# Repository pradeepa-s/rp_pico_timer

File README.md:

# rp_pico_timer
A simple timer that is started as a reminder to drink water.

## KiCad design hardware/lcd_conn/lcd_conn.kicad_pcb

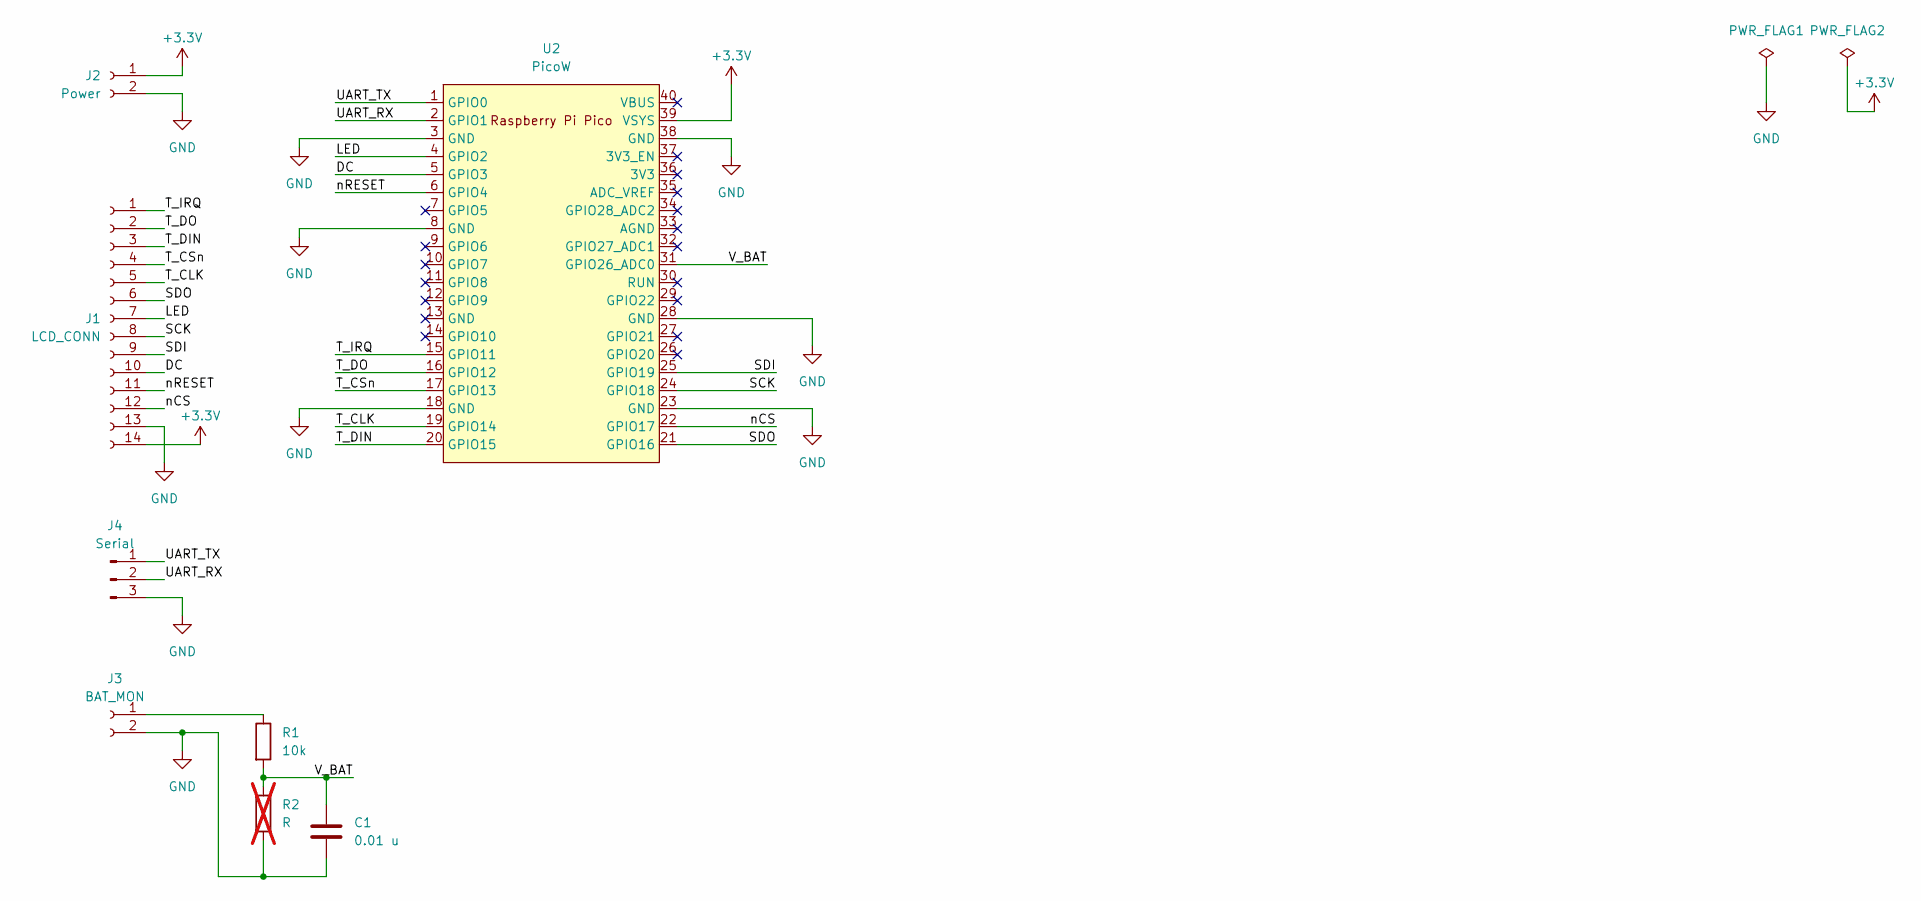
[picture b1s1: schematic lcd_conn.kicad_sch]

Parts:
C1: 0.01 u; C_Disc_D3.0mm_W2.0mm_P2.50mm
J1: LCD_CONN; PinSocket_1x14_P2.54mm_Vertical
J2: Power; PinHeader_1x02_P2.54mm_Vertical
J3: BAT_MON; PinHeader_1x02_P2.54mm_Vertical
J4: Serial; PinHeader_1x03_P2.54mm_Vertical
R1: 10k; R_Axial_DIN0207_L6.3mm_D2.5mm_P10.16mm_Horizontal
R2: R; R_Axial_DIN0207_L6.3mm_D2.5mm_P10.16mm_Horizontal; not fitted
U2: PicoW; RPi_PicoW_SMD_TH_CONN

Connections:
+3.3V: J1.14, J2.1, U2.39 (VSYS)
/DC: J1.10, U2.5 (GPIO3)
/LED: J1.7, U2.4 (GPIO2)
/SCK: J1.8, U2.24 (GPIO18)
/SDI: J1.9, U2.25 (GPIO19)
/SDO: J1.6, U2.21 (GPIO16)
/T_CLK: J1.5, U2.19 (GPIO14)
/T_CSn: J1.4, U2.17 (GPIO13)
/T_DIN: J1.3, U2.20 (GPIO15)
/T_DO: J1.2, U2.16 (GPIO12)
/T_IRQ: J1.1, U2.15 (GPIO11)
/UART_RX: J4.2, U2.2 (GPIO1)
/UART_TX: J4.1, U2.1 (GPIO0)
/V_BAT: C1.1, R1.2, R2.1, U2.31 (GPIO26_ADC0)
/nCS: J1.12, U2.22 (GPIO17)
/nRESET: J1.11, U2.6 (GPIO4)
GND: C1.2, J1.13, J2.2, J3.2, J4.3, R2.2, U2.3 (GND), U2.8 (GND), U2.18 (GND), U2.23 (GND), U2.28 (GND), U2.38 (GND)
unnamed: J3.1, R1.1

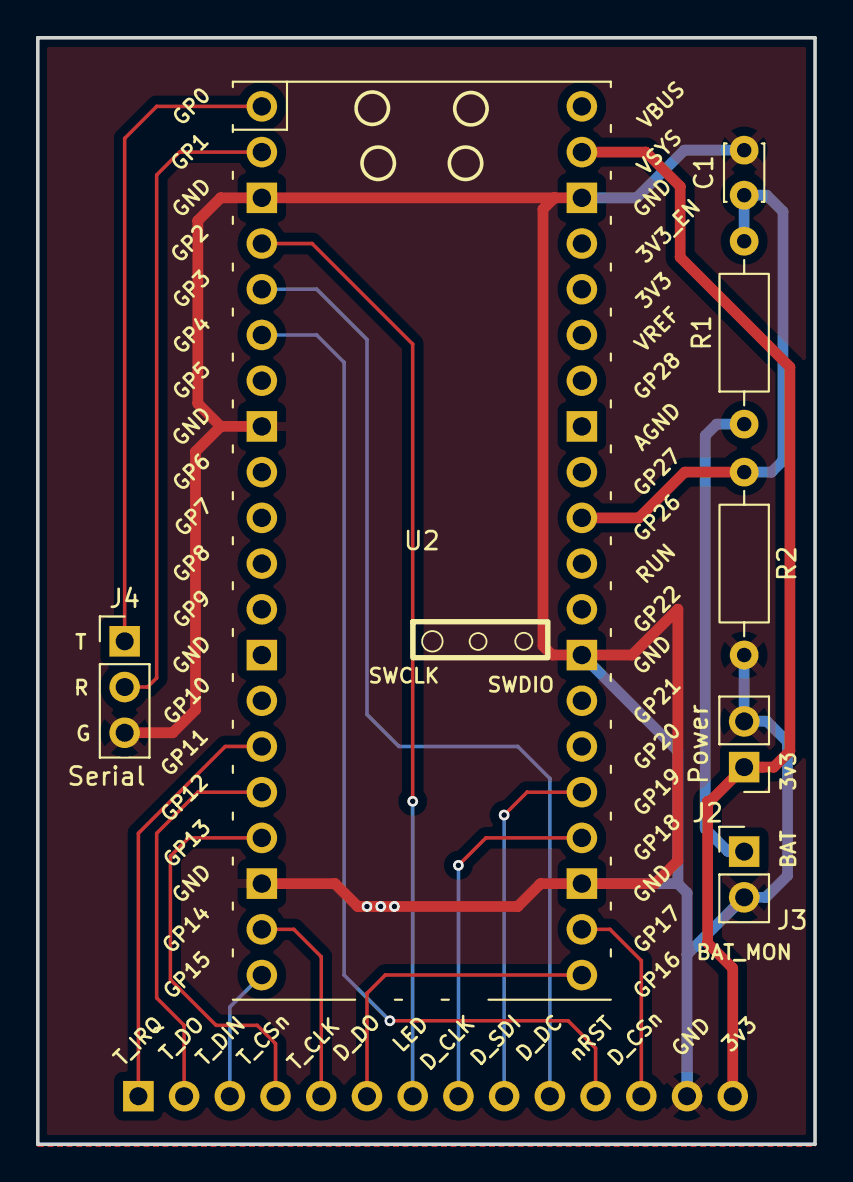
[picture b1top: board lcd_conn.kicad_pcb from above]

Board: 2 copper layers, 43.2 x 61.5 mm, 8 parts (1 on the bottom side), 18 nets.

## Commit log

2025-05-31 Changed folder
2025-05-31 Started
2025-05-31 Added a debug message emitter
2025-05-31 Added the reset button and logic
2025-05-31 Added an interface to read the touch point.
    * Cleaned up the touch_screen file.
2025-05-31 Added button
2025-05-31 Timer logic and screens redisgned, confirmed operation
2025-05-31 Adding lvgl
2025-05-31 Crude implementation of the touch screen
2025-05-31 Added improvements comment
2025-05-31 Added hr min incr decr buttons
2025-05-31 Clock ticks
2025-05-31 Start and stop works
2025-05-31 Allocated buffers for lcd
2025-05-31 Enabled LCD driver
2025-05-31 Blinking red clock
2025-05-31 Start - Stop button change based on touch
2025-05-31 Added timer and clock labels
2025-05-31 Hello, world is working
2025-05-31 Fixed set time screen button height
2025-06-25 Removed cy43 lib
2025-06-29 Added battery monitor
2025-06-29 Adding hardware
